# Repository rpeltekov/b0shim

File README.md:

# b0Shimming Project

Working to simulate and show that it is possible to correct for b0 inhomogeneity
caused by a TMS coil using a headcap of flexible and conforming RF coils 
designed by Julian Maravilla. They have been modified to be AC/DC.

* Contains modifications on code initially by Jacob White, Nicolas Arango, and Irene Kuang at MIT, "who have developed a low-cost 8-channel digitally-programmable current driver that can supply up to 8 amps DC per channel (up to 60 volt output). The circuit board design and control software were created by Nicolas Arango and Irene Kuang." More info can be found [here](https://rflab.martinos.org/index.php/Current_driver:Current_driver)

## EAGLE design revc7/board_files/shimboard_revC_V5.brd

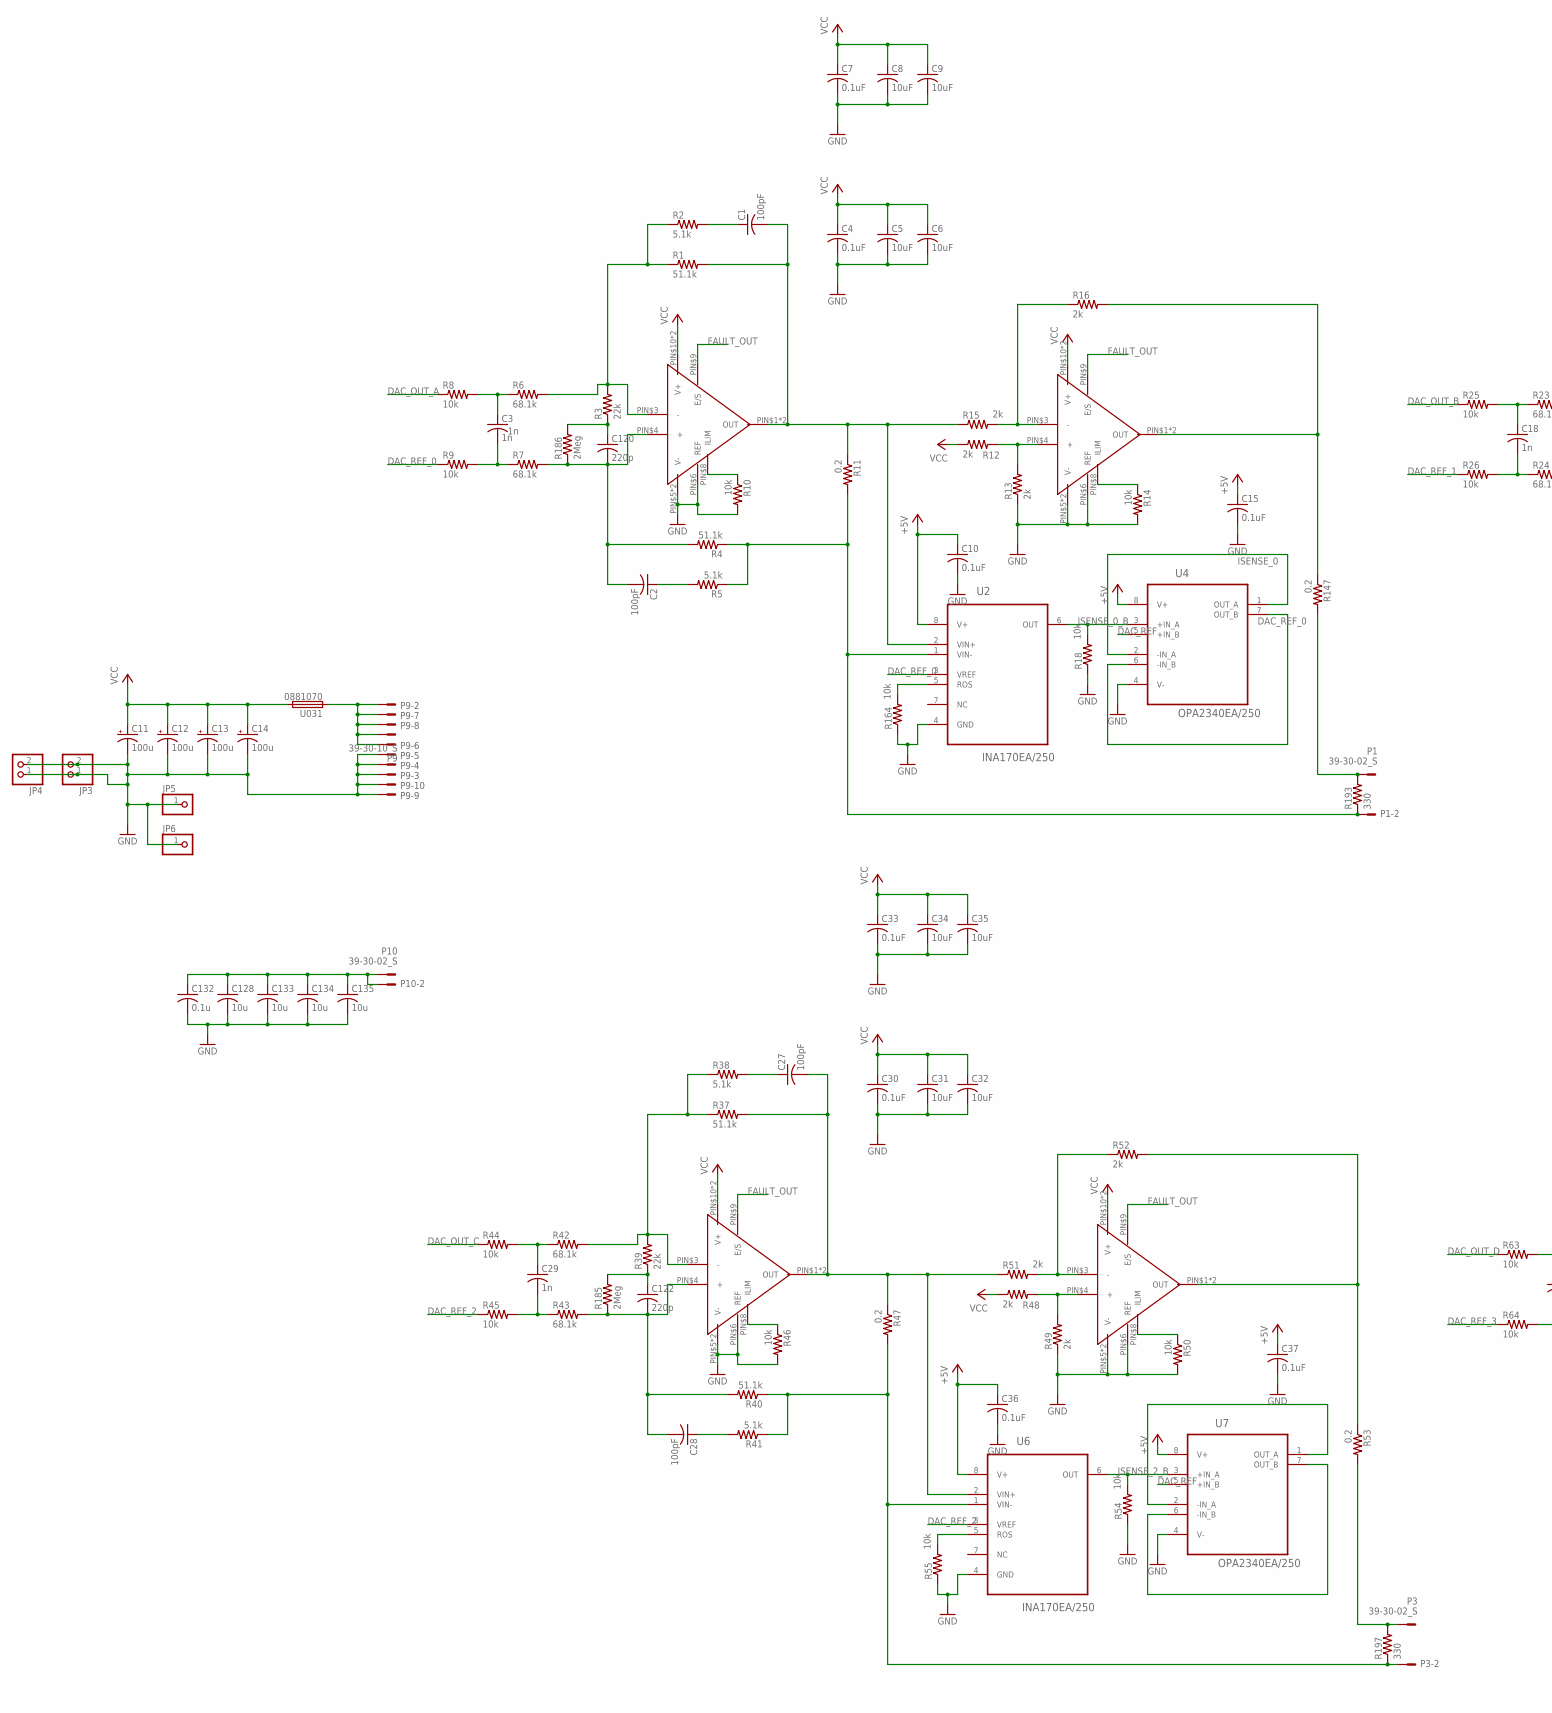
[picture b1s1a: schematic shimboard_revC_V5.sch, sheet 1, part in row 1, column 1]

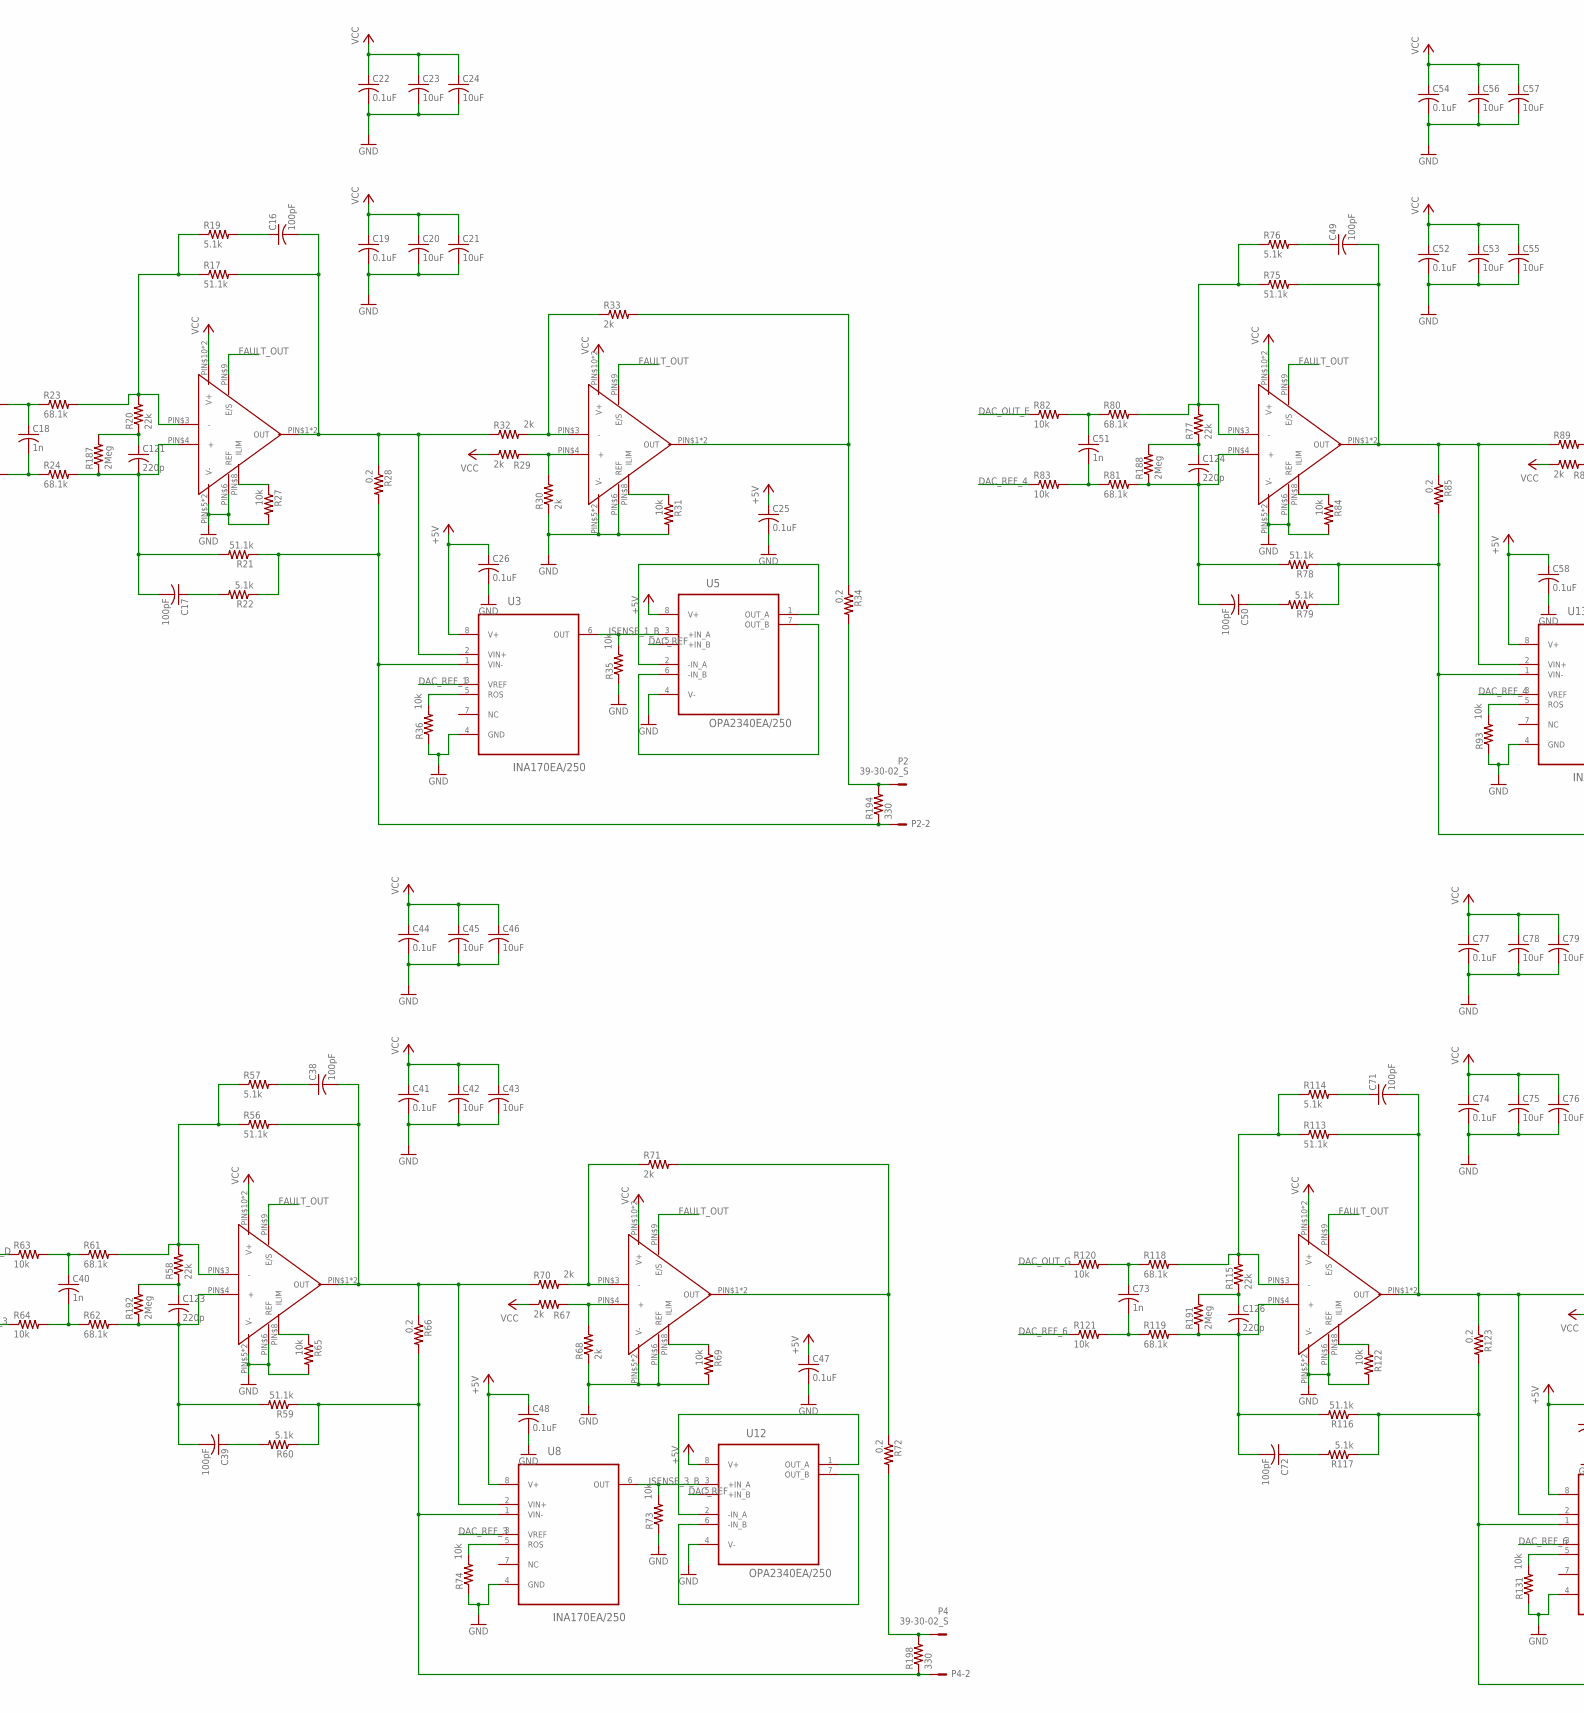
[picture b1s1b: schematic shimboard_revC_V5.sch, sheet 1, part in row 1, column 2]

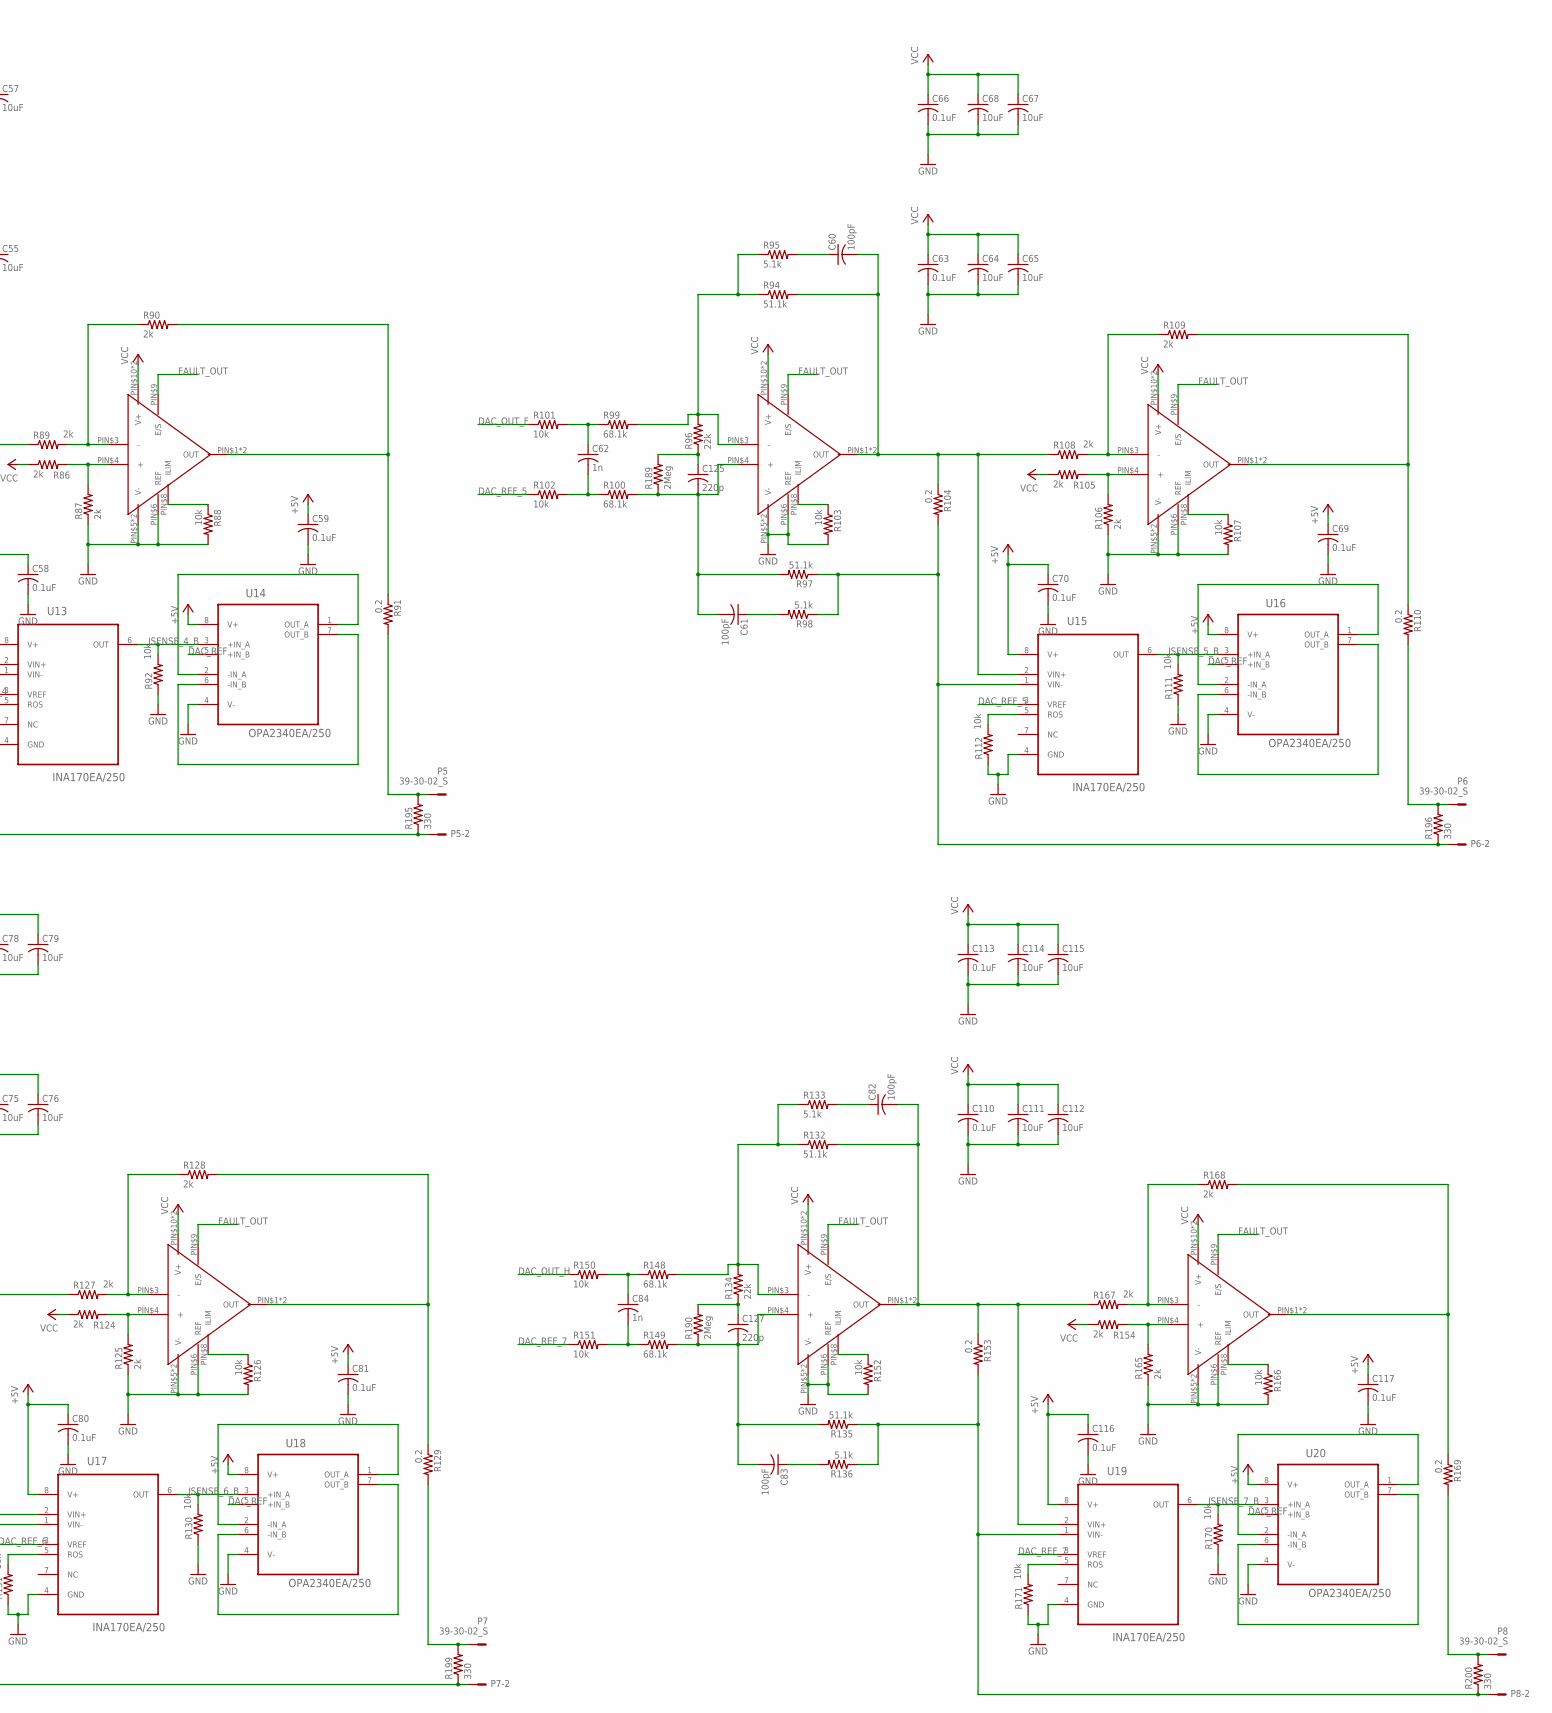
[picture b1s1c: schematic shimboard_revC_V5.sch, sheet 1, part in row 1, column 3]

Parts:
C1, C2, C16, C17, C27, C28, C38, C39, C49, C50, C60, C61, C71, C72, C82, C83: 100pF; C0805
C3, C18, C29, C40, C51, C62, C73, C84: 1n; C0805
C4, C7, C10, C15, C19, C22, C25, C26, C30, C33, C36, C37, C41, C44, C47, C48, C52, C54, C58, C59, C63, C66, C69, C70, C74, C77, C80, C81, C110, C113, C116, C117: 0.1uF; C0805
C5, C6, C8, C9, C20, C21, C23, C24, C31, C32, C34, C35, C42, C43, C45, C46, C53, C55, C56, C57, C64, C65, C67, C68, C75, C76, C78, C79, C111, C112, C114, C115: 10uF; C1206
C11, C12, C13, C14: 100u; D/7343-31W
C120, C121, C122, C123, C124, C125, C126, C127: 220p; C0805
C128, C133, C134, C135: 10u; C1206
C132: 0.1u; C0805
JP3, JP4: PINHD-1X2; 1X02
JP5, JP6: PINHD-1X1; 1X01
P1, P2, P3, P4, P5, P6, P7, P8, P10: 39-30-02_S; 39-30-?02?
P9: 39-30-10_S; 39-30-?10?
R1, R4, R17, R21, R37, R40, R56, R59, R75, R78, R94, R97, R113, R116, R132, R135: 51.1k; R0805
R2, R5, R19, R22, R38, R41, R57, R60, R76, R79, R95, R98, R114, R117, R133, R136: 5.1k; R0805
R3, R20, R39, R58, R77, R96, R115, R134: 22k; R0805
R6, R7, R23, R24, R42, R43, R61, R62, R80, R81, R99, R100, R118, R119, R148, R149: 68.1k; R0805
R8, R9, R10, R14, R18, R25, R26, R27, R31, R35, R36, R44, R45, R46, R50, R54, R55, R63, R64, R65, R69, R73, R74, R82, R83, R84, R88, R92, R93, R101, R102, R103, R107, R111, R112, R120, R121, R122, R126, R130, R131, R150, R151, R152, R164, R166, R170, R171: 10k; R0805
R11, R28, R34, R47, R53, R66, R72, R85, R91, R104, R110, R123, R129, R147, R153, R169: 0.2; R4527
R12, R29, R48, R67, R86, R105, R124, R154: 2k; M0805
R13, R15, R16, R30, R32, R33, R49, R51, R52, R68, R70, R71, R87, R89, R90, R106, R108, R109, R125, R127, R128, R165, R167, R168: 2k; R0805
R185, R186, R187, R188, R189, R190, R191, R192: 2Meg; R0805
R193, R194, R195, R196, R197, R198, R199, R200: 330; R2512
U2, U3, U6, U8, U13, U15, U17, U19: INA170EA/250; SOP65P490X110-8N
U4, U5, U7, U12, U14, U16, U18, U20: OPA2340EA/250; SOP65P490X110-8N
U031: 0881070; 881
U$1, U$2, U$3, U$4, U$5, U$6, U$7, U$8, U$9, U$10, U$11, U$12, U$13, U$14, U$15, U$16: OPA549_HS677NOHS; OPA549

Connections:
+5V: C10.1, C15.1, C25.1, C26.1, C36.1, C37.1, C47.1, C48.1, C58.1, C59.1, C69.1, C70.1, C80.1, C81.1, C116.1, C117.1, U2.8 (V+), U3.8 (V+), U4.8 (V+), U5.8 (V+), U6.8 (V+), U7.8 (V+), U8.8 (V+), U12.8 (V+), U13.8 (V+), U14.8 (V+), U15.8 (V+), U16.8 (V+), U17.8 (V+), U18.8 (V+), U19.8 (V+), U20.8 (V+); also elsewhere on the board
C0_O0: P1.2, R4.1, R5.1, R11.2, R193.1, U2.1 (VIN-)
C0_O1: P1.1, R147.2, R193.2
C1_O0: P2.2, R21.1, R22.1, R28.2, R194.1, U3.1 (VIN-)
C1_O1: P2.1, R34.2, R194.2
C2_O0: P3.2, R40.1, R41.1, R47.2, R197.1, U6.1 (VIN-)
C2_O1: P3.1, R53.2, R197.2
C3_O0: P4.2, R59.1, R60.1, R66.2, R198.1, U8.1 (VIN-)
C3_O1: P4.1, R72.2, R198.2
C4_O0: P5.2, R78.1, R79.1, R85.2, R195.1, U13.1 (VIN-)
C4_O1: P5.1, R91.2, R195.2
C5_O0: P6.2, R97.1, R98.1, R104.2, R196.1, U15.1 (VIN-)
C5_O1: P6.1, R110.2, R196.2
C6_O0: P7.1, R129.2, R199.2
C6_O1: P7.2, R116.1, R117.1, R123.2, R199.1, U17.1 (VIN-)
C7_O0: P8.2, R135.1, R136.1, R153.2, R200.1, U19.1 (VIN-)
C7_O1: P8.1, R169.2, R200.2
DAC_OUT_A: R8.1; also elsewhere on the board
DAC_OUT_B: R25.1; also elsewhere on the board
DAC_OUT_C: R44.1; also elsewhere on the board
DAC_OUT_D: R63.1; also elsewhere on the board
DAC_OUT_E: R82.1; also elsewhere on the board
DAC_OUT_F: R101.1; also elsewhere on the board
DAC_OUT_G: R120.1; also elsewhere on the board
DAC_OUT_H: R150.1; also elsewhere on the board
DAC_REF: U4.5 (+IN_B), U5.5 (+IN_B), U7.5 (+IN_B), U12.5 (+IN_B), U14.5 (+IN_B), U16.5 (+IN_B), U18.5 (+IN_B), U20.5 (+IN_B); also elsewhere on the board
DAC_REF_0: R9.1, U2.3 (VREF), U4.6 (-IN_B), U4.7 (OUT_B)
DAC_REF_1: R26.1, U3.3 (VREF), U5.6 (-IN_B), U5.7 (OUT_B)
DAC_REF_2: R45.1, U6.3 (VREF), U7.6 (-IN_B), U7.7 (OUT_B)
DAC_REF_3: R64.1, U8.3 (VREF), U12.6 (-IN_B), U12.7 (OUT_B)
DAC_REF_4: R83.1, U13.3 (VREF), U14.6 (-IN_B), U14.7 (OUT_B)
DAC_REF_5: R102.1, U15.3 (VREF), U16.6 (-IN_B), U16.7 (OUT_B)
DAC_REF_6: R121.1, U17.3 (VREF), U18.6 (-IN_B), U18.7 (OUT_B)
DAC_REF_7: R151.1, U19.3 (VREF), U20.6 (-IN_B), U20.7 (OUT_B)
FAULT_OUT: U$1.PIN$9 (E/S), U$2.PIN$9 (E/S), U$3.PIN$9 (E/S), U$4.PIN$9 (E/S), U$5.PIN$9 (E/S), U$6.PIN$9 (E/S), U$7.PIN$9 (E/S), U$8.PIN$9 (E/S), U$9.PIN$9 (E/S), U$10.PIN$9 (E/S), U$11.PIN$9 (E/S), U$12.PIN$9 (E/S), U$13.PIN$9 (E/S), U$14.PIN$9 (E/S), U$15.PIN$9 (E/S), U$16.PIN$9 (E/S); also elsewhere on the board
GND: C4.2, C5.2, C6.2, C7.2, C8.2, C9.2, C10.2, C11.-, C12.-, C13.-, C14.-, C15.2, C19.2, C20.2, C21.2, C22.2, C23.2, C24.2, C25.2, C26.2, C30.2, C31.2, C32.2, C33.2, C34.2, C35.2, C36.2, C37.2, C41.2, C42.2, C43.2, C44.2, C45.2, C46.2, C47.2, C48.2, C52.2, C53.2, C54.2, C55.2, C56.2, C57.2, C58.2, C59.2, C63.2, C64.2, C65.2, C66.2, C67.2, C68.2, C69.2, C70.2, C74.2, C75.2, C76.2, C77.2, C78.2, C79.2, C80.2, C81.2, C110.2, C111.2, C112.2, C113.2, C114.2, C115.2, C116.2, C117.2, C128.2, C132.2, C133.2, C134.2, C135.2, JP3.1, JP3.2, JP4.1, JP4.2, JP5.1, JP6.1, P9.3, P9.4, P9.5, P9.9, P9.10, R10.2, R13.1, R14.2, R18.1, R27.2, R30.1, R31.2, R35.1, R36.1, R46.2, R49.1, R50.2, R54.1, R55.1, R65.2, R68.1, R69.2, R73.1, R74.1, R84.2, R87.1, R88.2, R92.1, R93.1, R103.2, R106.1, R107.2, R111.1, R112.1, R122.2, R125.1, R126.2, R130.1, R131.1, R152.2, R164.1, R165.1, R166.2, R170.1, R171.1, U2.4 (GND), U3.4 (GND), U4.4 (V-), U5.4 (V-), U6.4 (GND), U7.4 (V-), U8.4 (GND), U12.4 (V-), U13.4 (GND), U14.4 (V-), U15.4 (GND), U16.4 (V-), U17.4 (GND), U18.4 (V-), U19.4 (GND), U20.4 (V-), U$1.PIN$5 (V-), U$1.PIN$6 (REF), U$1.PIN$7 (V-), U$2.PIN$5 (V-), U$2.PIN$6 (REF), U$2.PIN$7 (V-), U$3.PIN$5 (V-), U$3.PIN$6 (REF), U$3.PIN$7 (V-), U$4.PIN$5 (V-), U$4.PIN$6 (REF), U$4.PIN$7 (V-), U$5.PIN$5 (V-), U$5.PIN$6 (REF), U$5.PIN$7 (V-), U$6.PIN$5 (V-), U$6.PIN$6 (REF), U$6.PIN$7 (V-), U$7.PIN$5 (V-), U$7.PIN$6 (REF), U$7.PIN$7 (V-), U$8.PIN$5 (V-), U$8.PIN$6 (REF), U$8.PIN$7 (V-), U$9.PIN$5 (V-), U$9.PIN$6 (REF), U$9.PIN$7 (V-), U$10.PIN$5 (V-), U$10.PIN$6 (REF), U$10.PIN$7 (V-), U$11.PIN$5 (V-), U$11.PIN$6 (REF), U$11.PIN$7 (V-), U$12.PIN$5 (V-), U$12.PIN$6 (REF), U$12.PIN$7 (V-), U$13.PIN$5 (V-), U$13.PIN$6 (REF), U$13.PIN$7 (V-), U$14.PIN$5 (V-), U$14.PIN$6 (REF), U$14.PIN$7 (V-), U$15.PIN$5 (V-), U$15.PIN$6 (REF), U$15.PIN$7 (V-), U$16.PIN$5 (V-), U$16.PIN$6 (REF), U$16.PIN$7 (V-); also elsewhere on the board
ISENSE_0: U4.1 (OUT_A), U4.2 (-IN_A); also elsewhere on the board
ISENSE_0_B: R18.2, U2.6 (OUT), U4.3 (+IN_A)
ISENSE_1: U5.1 (OUT_A), U5.2 (-IN_A); also elsewhere on the board
ISENSE_1_B: R35.2, U3.6 (OUT), U5.3 (+IN_A)
ISENSE_2: U7.1 (OUT_A), U7.2 (-IN_A); also elsewhere on the board
ISENSE_2_B: R54.2, U6.6 (OUT), U7.3 (+IN_A)
ISENSE_3: U12.1 (OUT_A), U12.2 (-IN_A); also elsewhere on the board
ISENSE_3_B: R73.2, U8.6 (OUT), U12.3 (+IN_A)
ISENSE_4: U14.1 (OUT_A), U14.2 (-IN_A); also elsewhere on the board
ISENSE_4_B: R92.2, U13.6 (OUT), U14.3 (+IN_A)
ISENSE_5: U16.1 (OUT_A), U16.2 (-IN_A); also elsewhere on the board
ISENSE_5_B: R111.2, U15.6 (OUT), U16.3 (+IN_A)
ISENSE_6: U18.1 (OUT_A), U18.2 (-IN_A); also elsewhere on the board
ISENSE_6_B: R130.2, U17.6 (OUT), U18.3 (+IN_A)
ISENSE_7: U20.1 (OUT_A), U20.2 (-IN_A); also elsewhere on the board
ISENSE_7_B: R170.2, U19.6 (OUT), U20.3 (+IN_A)
unnamed: R1.1, R2.1, R3.2, R6.2, U$1.PIN$3 (-)
unnamed: C1.1, R2.2
unnamed: R17.1, R19.1, R20.2, R23.2, U$3.PIN$3 (-)
unnamed: C3.2, R7.1, R9.2
unnamed: C2.2, C120.2, R4.2, R7.2, R186.1, U$1.PIN$4 (+)
unnamed: C2.1, R5.2
unnamed: C3.1, R6.1, R8.2
unnamed: R12.2, R13.2, U$2.PIN$4 (+)
unnamed: C16.1, R19.2
unnamed: C17.2, C121.2, R21.2, R24.2, R187.1, U$3.PIN$4 (+)
unnamed: R10.1, U$1.PIN$8 (ILIM)
unnamed: R15.2, R16.1, U$2.PIN$3 (-)
unnamed: C17.1, R22.2
unnamed: R14.1, U$2.PIN$8 (ILIM)
unnamed: C1.2, R1.2, R11.1, R15.1, U2.2 (VIN+), U$1.PIN$1 (OUT), U$1.PIN$2 (OUT)
unnamed: C18.2, R24.1, R26.2
unnamed: C18.1, R23.1, R25.2
unnamed: R27.1, U$3.PIN$8 (ILIM)
unnamed: R29.2, R30.2, U$4.PIN$4 (+)
unnamed: R31.1, U$4.PIN$8 (ILIM)
unnamed: R32.2, R33.1, U$4.PIN$3 (-)
unnamed: C16.2, R17.2, R28.1, R32.1, U3.2 (VIN+), U$3.PIN$1 (OUT), U$3.PIN$2 (OUT)
unnamed: R33.2, R34.1, U$4.PIN$1 (OUT), U$4.PIN$2 (OUT)
unnamed: R36.2, U3.5 (ROS)
unnamed: R37.1, R38.1, R39.2, R42.2, U$5.PIN$3 (-)
unnamed: C27.1, R38.2
unnamed: C28.2, C122.2, R40.2, R43.2, R185.1, U$5.PIN$4 (+)
unnamed: C28.1, R41.2
unnamed: C29.2, R43.1, R45.2
unnamed: C29.1, R42.1, R44.2
unnamed: R46.1, U$5.PIN$8 (ILIM)
unnamed: R48.2, R49.2, U$6.PIN$4 (+)
unnamed: R50.1, U$6.PIN$8 (ILIM)
unnamed: R51.2, R52.1, U$6.PIN$3 (-)
unnamed: C27.2, R37.2, R47.1, R51.1, U6.2 (VIN+), U$5.PIN$1 (OUT), U$5.PIN$2 (OUT)
unnamed: R52.2, R53.1, U$6.PIN$1 (OUT), U$6.PIN$2 (OUT)
unnamed: R55.2, U6.5 (ROS)
unnamed: R56.1, R57.1, R58.2, R61.2, U$7.PIN$3 (-)
unnamed: C38.1, R57.2
unnamed: C39.2, C123.2, R59.2, R62.2, R192.1, U$7.PIN$4 (+)
unnamed: C39.1, R60.2
unnamed: C40.2, R62.1, R64.2
unnamed: C40.1, R61.1, R63.2
unnamed: R65.1, U$7.PIN$8 (ILIM)
unnamed: R67.2, R68.2, U$8.PIN$4 (+)
unnamed: R69.1, U$8.PIN$8 (ILIM)
unnamed: R70.2, R71.1, U$8.PIN$3 (-)
unnamed: C38.2, R56.2, R66.1, R70.1, U8.2 (VIN+), U$7.PIN$1 (OUT), U$7.PIN$2 (OUT)
unnamed: R71.2, R72.1, U$8.PIN$1 (OUT), U$8.PIN$2 (OUT)
unnamed: R74.2, U8.5 (ROS)
unnamed: R75.1, R76.1, R77.2, R80.2, U$9.PIN$3 (-)
unnamed: C49.1, R76.2
unnamed: C50.2, C124.2, R78.2, R81.2, R188.1, U$9.PIN$4 (+)
unnamed: C50.1, R79.2
unnamed: C51.2, R81.1, R83.2
unnamed: C51.1, R80.1, R82.2
unnamed: R84.1, U$9.PIN$8 (ILIM)
unnamed: R86.2, R87.2, U$10.PIN$4 (+)
unnamed: R88.1, U$10.PIN$8 (ILIM)
unnamed: R89.2, R90.1, U$10.PIN$3 (-)
unnamed: C49.2, R75.2, R85.1, R89.1, U13.2 (VIN+), U$9.PIN$1 (OUT), U$9.PIN$2 (OUT)
unnamed: R90.2, R91.1, U$10.PIN$1 (OUT), U$10.PIN$2 (OUT)
unnamed: R93.2, U13.5 (ROS)
unnamed: R94.1, R95.1, R96.2, R99.2, U$11.PIN$3 (-)
unnamed: C60.1, R95.2
unnamed: C83.2, C127.2, R135.2, R149.2, R190.1, U$15.PIN$4 (+)
unnamed: C61.1, R98.2
unnamed: C62.2, R100.1, R102.2
unnamed: C62.1, R99.1, R101.2
unnamed: R103.1, U$11.PIN$8 (ILIM)
unnamed: R105.2, R106.2, U$12.PIN$4 (+)
unnamed: R107.1, U$12.PIN$8 (ILIM)
unnamed: R108.2, R109.1, U$12.PIN$3 (-)
unnamed: C60.2, R94.2, R104.1, R108.1, U15.2 (VIN+), U$11.PIN$1 (OUT), U$11.PIN$2 (OUT)
unnamed: R109.2, R110.1, U$12.PIN$1 (OUT), U$12.PIN$2 (OUT)
unnamed: R112.2, U15.5 (ROS)
unnamed: R113.1, R114.1, R115.2, R118.2, U$13.PIN$3 (-)
unnamed: C71.1, R114.2
unnamed: C72.2, C126.2, R116.2, R119.2, R191.1, U$13.PIN$4 (+)
unnamed: C72.1, R117.2
unnamed: C73.2, R119.1, R121.2
unnamed: C73.1, R118.1, R120.2
unnamed: R122.1, U$13.PIN$8 (ILIM)
unnamed: R124.2, R125.2, U$14.PIN$4 (+)
unnamed: R126.1, U$14.PIN$8 (ILIM)
unnamed: R127.2, R128.1, U$14.PIN$3 (-)
unnamed: C71.2, R113.2, R123.1, R127.1, U17.2 (VIN+), U$13.PIN$1 (OUT), U$13.PIN$2 (OUT)
unnamed: R128.2, R129.1, U$14.PIN$1 (OUT), U$14.PIN$2 (OUT)
unnamed: R131.2, U17.5 (ROS)
unnamed: R132.1, R133.1, R134.2, R148.2, U$15.PIN$3 (-)
unnamed: C82.1, R133.2
unnamed: C83.1, R136.2
unnamed: C84.2, R149.1, R151.2
unnamed: C84.1, R148.1, R150.2
unnamed: R152.1, U$15.PIN$8 (ILIM)
unnamed: R16.2, R147.1, U$2.PIN$1 (OUT), U$2.PIN$2 (OUT)
unnamed: R154.2, R165.2, U$16.PIN$4 (+)
unnamed: C128.1, C132.1, C133.1, C134.1, C135.1, P10.1, P10.2
unnamed: R166.1, U$16.PIN$8 (ILIM)
unnamed: R167.2, R168.1, U$16.PIN$3 (-)
unnamed: C82.2, R132.2, R153.1, R167.1, U19.2 (VIN+), U$15.PIN$1 (OUT), U$15.PIN$2 (OUT)
unnamed: R168.2, R169.1, U$16.PIN$1 (OUT), U$16.PIN$2 (OUT)
unnamed: R171.2, U19.5 (ROS)
unnamed: R164.2, U2.5 (ROS)
unnamed: C61.2, C125.2, R97.2, R100.2, R189.1, U$11.PIN$4 (+)
unnamed: C120.1, R3.1, R186.2
unnamed: C121.1, R20.1, R187.2
unnamed: C124.1, R77.1, R188.2
unnamed: C125.1, R96.1, R189.2
unnamed: C122.1, R39.1, R185.2
unnamed: C123.1, R58.1, R192.2
unnamed: C126.1, R115.1, R191.2
unnamed: C127.1, R134.1, R190.2
VCC: C4.1, C5.1, C6.1, C7.1, C8.1, C9.1, C11.+, C12.+, C13.+, C14.+, C19.1, C20.1, C21.1, C22.1, C23.1, C24.1, C30.1, C31.1, C32.1, C33.1, C34.1, C35.1, C41.1, C42.1, C43.1, C44.1, C45.1, C46.1, C52.1, C53.1, C54.1, C55.1, C56.1, C57.1, C63.1, C64.1, C65.1, C66.1, C67.1, C68.1, C74.1, C75.1, C76.1, C77.1, C78.1, C79.1, C110.1, C111.1, C112.1, C113.1, C114.1, C115.1, R12.1, R29.1, R48.1, R67.1, R86.1, R105.1, R124.1, R154.1, U031.P$2 (2), U$1.PIN$10 (V+), U$1.PIN$11 (V+), U$2.PIN$10 (V+), U$2.PIN$11 (V+), U$3.PIN$10 (V+), U$3.PIN$11 (V+), U$4.PIN$10 (V+), U$4.PIN$11 (V+), U$5.PIN$10 (V+), U$5.PIN$11 (V+), U$6.PIN$10 (V+), U$6.PIN$11 (V+), U$7.PIN$10 (V+), U$7.PIN$11 (V+), U$8.PIN$10 (V+), U$8.PIN$11 (V+), U$9.PIN$10 (V+), U$9.PIN$11 (V+), U$10.PIN$10 (V+), U$10.PIN$11 (V+), U$11.PIN$10 (V+), U$11.PIN$11 (V+), U$12.PIN$10 (V+), U$12.PIN$11 (V+), U$13.PIN$10 (V+), U$13.PIN$11 (V+), U$14.PIN$10 (V+), U$14.PIN$11 (V+), U$15.PIN$10 (V+), U$15.PIN$11 (V+), U$16.PIN$10 (V+), U$16.PIN$11 (V+); also elsewhere on the board
VCC_I: P9.1, P9.2, P9.6, P9.7, P9.8, U031.P$1 (1)

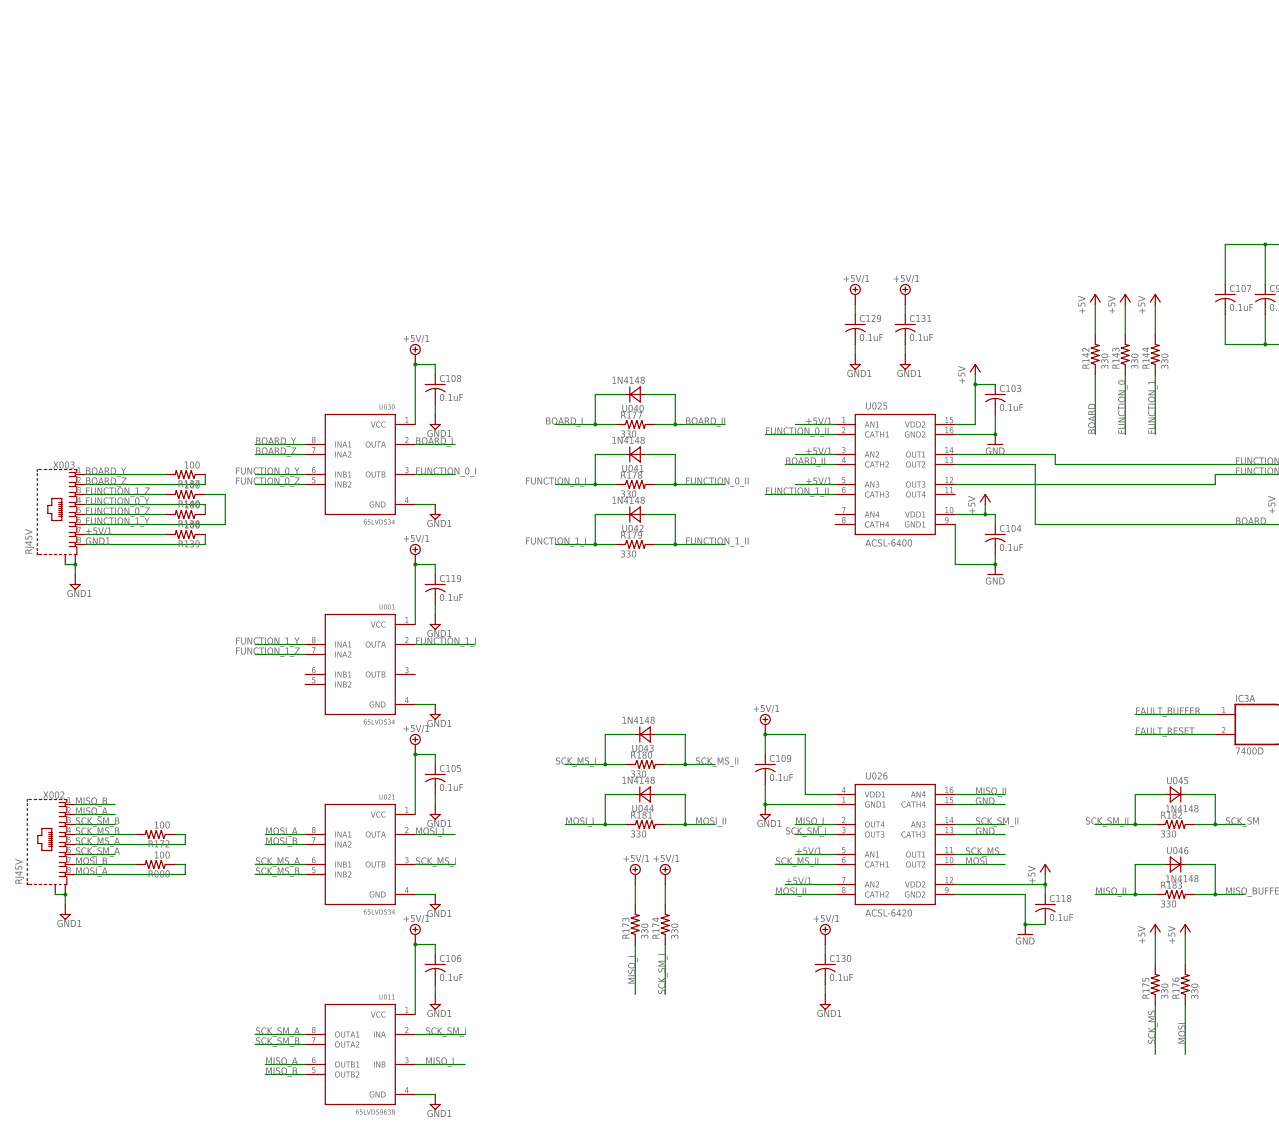
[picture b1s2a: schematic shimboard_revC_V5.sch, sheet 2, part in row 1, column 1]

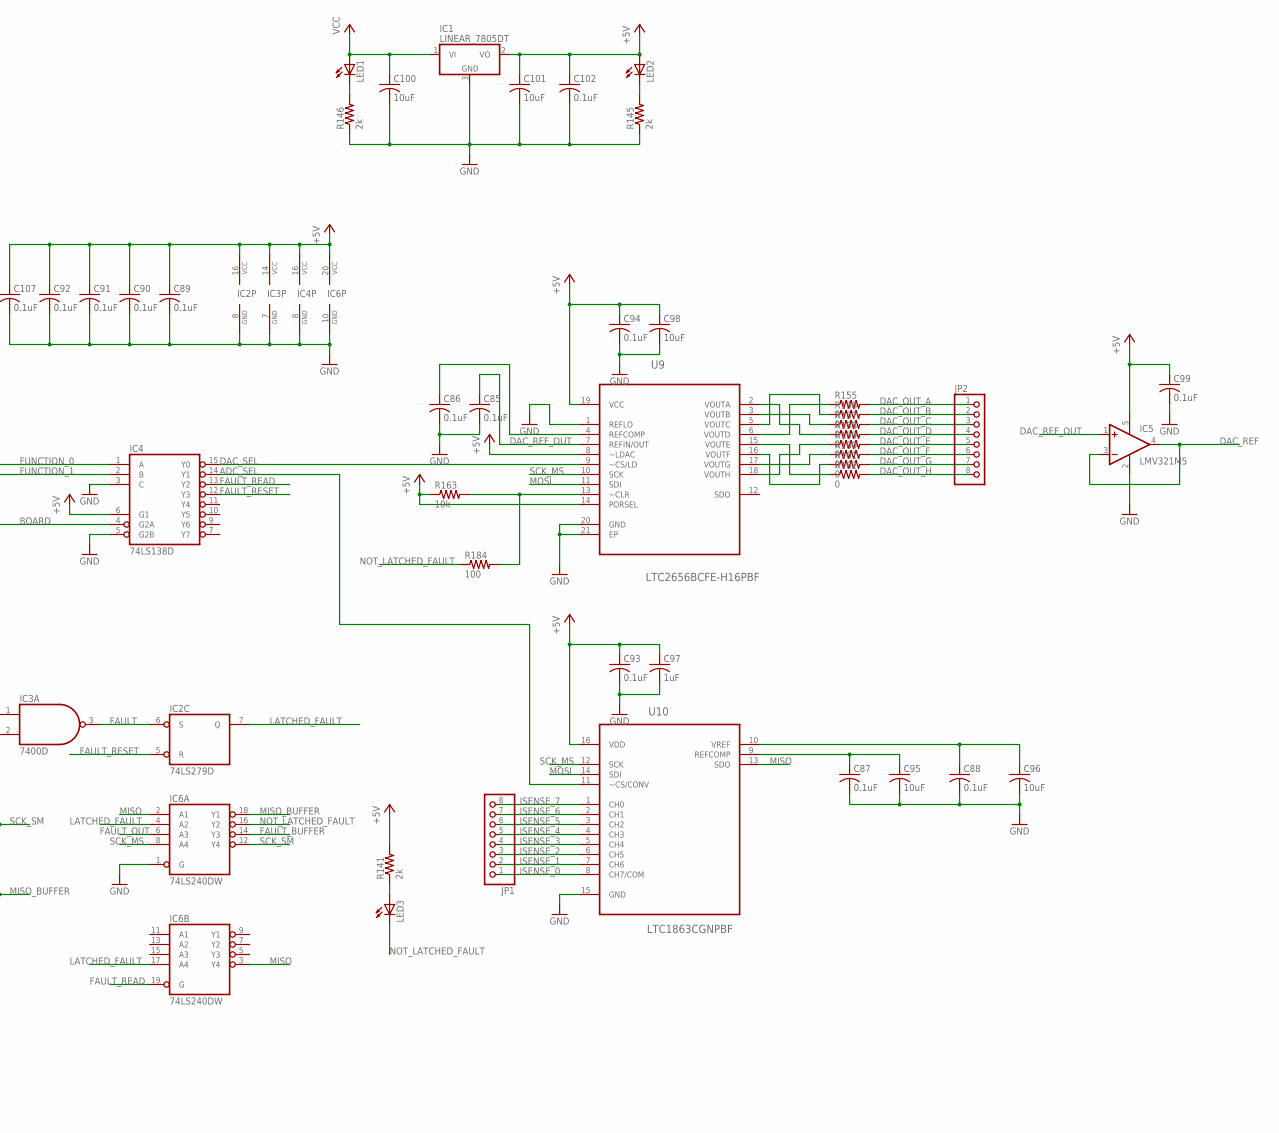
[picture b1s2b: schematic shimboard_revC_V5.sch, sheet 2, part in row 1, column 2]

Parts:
C85, C86, C87, C88, C89, C90, C91, C92, C93, C94, C99, C102, C103, C104, C105, C106, C107, C108, C109, C118, C119, C129, C130, C131: 0.1uF; C0603
C95, C96, C98, C100, C101: 10uF; C1206
C97: 1uF; C0603
IC1: LINEAR_7805DT; LINEAR_TO252
IC2: 74LS279D; SO16
IC3: 7400D; SO14
IC4: 74LS138D; SO16
IC5: LMV321M5; SOT23-5
IC6: 74LS240DW; SO20W
JP1, JP2: PINHD-1X8; 1X08
LED1, LED2, LED3: LEDCHIPLED_0805; CHIPLED_0805
R000, R137, R138, R139, R140, R172, R184: 100; R0805
R141, R145, R146: 2k; R0805
R142, R143, R144, R173, R174, R175, R176, R177, R178, R179, R180, R181, R182, R183: 330; R0805
R155, R156, R157, R158, R159, R160, R161, R162: 0; R0603
R163: 10k; R0603
U001, U021, U030: 65LVDS34; SO08-1
U9: LTC2656BCFE-H16PBF; SOP65P640X120-21N
U10: LTC1863CGNPBF; SOP63P600X175-16N
U011: 65LVDS9638; SO08-1
U025: ACSL-6400; ACSL-SO16
U026: ACSL-6420; ACSL-SO16
U040, U041, U042, U043, U044, U045, U046: 1N4148
X002, X003: RJ45V; RJ45-VERTICAL

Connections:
+5V: C89.1, C90.1, C91.1, C92.1, C93.1, C94.1, C97.1, C98.1, C99.1, C101.1, C102.1, C103.1, C104.1, C107.1, C118.1, IC1.2 (VO), IC2.16 (VCC), IC3.14 (VCC), IC4.6 (G1), IC4.16 (VCC), IC5.5 (V+), IC6.20 (VCC), LED2.A, R141.2, R142.2, R143.2, R144.2, R163.1, R175.2, R176.2, U9.8 (~LDAC), U9.14 (PORSEL), U9.19 (VCC), U10.16 (VDD), U025.10 (VDD1), U025.15 (VDD2), U026.12 (VDD2); also elsewhere on the board
+5V/1: C105.1, C106.1, C108.1, C109.1, C119.1, C129.1, C130.1, C131.1, R139.2, R173.2, R174.2, U001.1 (VCC), U011.1 (VCC), U021.1 (VCC), U025.1 (AN1), U025.3 (AN2), U025.5 (AN3), U026.4 (VDD1), U026.5 (AN1), U026.7 (AN2), U030.1 (VCC), X003.7
ADC_SEL: IC4.14 (Y1), U10.11 (~CS/CONV)
BOARD: IC4.4 (G2A), R142.1, U025.13 (OUT2)
BOARD_I: R177.1, U030.2 (OUTA), U040.2 (C)
BOARD_II: R177.2, U025.4 (CATH2), U040.1 (A)
BOARD_Y: R137.2, U030.8 (INA1), X003.1
BOARD_Z: R137.1, U030.7 (INA2), X003.2
DAC_OUT_A: JP2.1, R155.2; also elsewhere on the board
DAC_OUT_B: JP2.2, R156.2; also elsewhere on the board
DAC_OUT_C: JP2.3, R157.2; also elsewhere on the board
DAC_OUT_D: JP2.4, R158.2; also elsewhere on the board
DAC_OUT_E: JP2.5, R159.2; also elsewhere on the board
DAC_OUT_F: JP2.6, R160.2; also elsewhere on the board
DAC_OUT_G: JP2.7, R161.2; also elsewhere on the board
DAC_OUT_H: JP2.8, R162.2; also elsewhere on the board
DAC_REF: IC5.3 (-IN), IC5.4 (OUT); also elsewhere on the board
DAC_REF_OUT: C85.1, IC5.1 (+IN), U9.7 (REFIN/OUT)
DAC_SEL: IC4.15 (Y0), U9.9 (~CS/LD)
FAULT: IC2.6 (S), IC3.3 (O)
FAULT_BUFFER: IC3.1 (I0), IC6.14 (Y3)
FAULT_OUT: IC6.6 (A3); also elsewhere on the board
FAULT_READ: IC4.13 (Y2), IC6.19 (G)
FAULT_RESET: IC2.5 (R), IC3.2 (I1), IC4.12 (Y3)
FUNCTION_0: IC4.1 (A), R143.1, U025.14 (OUT1)
FUNCTION_0_I: R178.1, U030.3 (OUTB), U041.2 (C)
FUNCTION_0_II: R178.2, U025.2 (CATH1), U041.1 (A)
FUNCTION_0_Y: R138.1, U030.6 (INB1), X003.4
FUNCTION_0_Z: R138.2, U030.5 (INB2), X003.5
FUNCTION_1: IC4.2 (B), R144.1, U025.12 (OUT3)
FUNCTION_1_I: R179.1, U001.2 (OUTA), U042.2 (C)
FUNCTION_1_II: R179.2, U025.6 (CATH3), U042.1 (A)
FUNCTION_1_Y: R140.1, U001.8 (INA1), X003.6
FUNCTION_1_Z: R140.2, U001.7 (INA2), X003.3
GND: C85.2, C86.2, C87.2, C88.2, C89.2, C90.2, C91.2, C92.2, C93.2, C94.2, C95.2, C96.2, C97.2, C98.2, C99.2, C100.2, C101.2, C102.2, C103.2, C104.2, C107.2, C118.2, IC1.3 (GND), IC2.8 (GND), IC3.7 (GND), IC4.3 (C), IC4.5 (G2B), IC4.8 (GND), IC5.2 (V-), IC6.1 (G), IC6.10 (GND), R145.1, R146.1, U9.1 (REFLO), U9.20 (GND), U9.21 (EP), U10.15 (GND), U025.9 (GND1), U025.16 (GND2), U026.9 (GND2), U026.13 (CATH3), U026.15 (CATH4); also elsewhere on the board
GND1: C105.2, C106.2, C108.2, C109.2, C119.2, C129.2, C130.2, C131.2, R139.1, U001.4 (GND), U011.4 (GND), U021.4 (GND), U026.1 (GND1), U030.4 (GND), X002.G1 (S), X002.G2 (S), X003.8, X003.G1 (S), X003.G2 (S)
ISENSE_0: JP1.1, U10.8 (CH7/COM); also elsewhere on the board
ISENSE_1: JP1.2, U10.7 (CH6); also elsewhere on the board
ISENSE_2: JP1.3, U10.6 (CH5); also elsewhere on the board
ISENSE_3: JP1.4, U10.5 (CH4); also elsewhere on the board
ISENSE_4: JP1.5, U10.4 (CH3); also elsewhere on the board
ISENSE_5: JP1.6, U10.3 (CH2); also elsewhere on the board
ISENSE_6: JP1.7, U10.2 (CH1); also elsewhere on the board
ISENSE_7: JP1.8, U10.1 (CH0); also elsewhere on the board
LATCHED_FAULT: IC2.7 (Q), IC6.4 (A2), IC6.17 (A4)
MISO: IC6.2 (A1), IC6.3 (Y4), U10.13 (SDO)
MISO_A: U011.6 (OUTB1), X002.2
MISO_B: U011.5 (OUTB2), X002.1
MISO_BUFFER: IC6.18 (Y1), R183.2, U046.2 (C)
MISO_I: R173.1, U011.3 (INB), U026.2 (OUT4)
MISO_II: R183.1, U026.16 (AN4), U046.1 (A)
MOSI: R176.1, U9.11 (SDI), U10.14 (SDI), U026.10 (OUT2)
MOSI_A: R000.1, U021.8 (INA1), X002.8
MOSI_B: R000.2, U021.7 (INA2), X002.7
MOSI_I: R181.1, U021.2 (OUTA), U044.2 (C)
MOSI_II: R181.2, U026.8 (CATH2), U044.1 (A)
unnamed: R155.1, U9.6 (VOUTD)
unnamed: R162.1, U9.15 (VOUTE)
unnamed: R159.1, U9.18 (VOUTH)
unnamed: R160.1, U9.17 (VOUTG)
unnamed: R161.1, U9.16 (VOUTF)
unnamed: R158.1, U9.2 (VOUTA)
unnamed: LED2.C, R145.2
unnamed: LED3.A, R141.1
unnamed: R163.2, R184.2, U9.13 (~CLR)
unnamed: LED1.C, R146.2
unnamed: C86.1, U9.4 (REFCOMP)
unnamed: C87.1, C95.1, U10.9 (REFCOMP)
unnamed: C88.1, C96.1, U10.10 (VREF)
unnamed: R157.1, U9.3 (VOUTB)
unnamed: R156.1, U9.5 (VOUTC)
NOT_LATCHED_FAULT: IC6.16 (Y2), LED3.C, R184.1
SCK_MS: IC6.8 (A4), R175.1, U9.10 (SCK), U10.12 (SCK), U026.11 (OUT1)
SCK_MS_A: R172.1, U021.6 (INB1), X002.5
SCK_MS_B: R172.2, U021.5 (INB2), X002.4
SCK_MS_I: R180.1, U021.3 (OUTB), U043.2 (C)
SCK_MS_II: R180.2, U026.6 (CATH1), U043.1 (A)
SCK_SM: IC6.12 (Y4), R182.2, U045.2 (C)
SCK_SM_A: U011.8 (OUTA1), X002.6
SCK_SM_B: U011.7 (OUTA2), X002.3
SCK_SM_I: R174.1, U011.2 (INA), U026.3 (OUT3)
SCK_SM_II: R182.1, U026.14 (AN3), U045.1 (A)
VCC: C100.1, IC1.1 (VI), LED1.A; also elsewhere on the board

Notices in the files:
parts and their libraries:
con-molex-mini-fit: Copyright (C) 2011, Bob Starr
SparkFun-Passives: Licensing: CC v3.0 Share-Alike You are welcome to use this library for commercial purposes.
